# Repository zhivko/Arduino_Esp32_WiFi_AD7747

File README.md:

# D-duino-32(ESP32&0.96OLED display) & AD7747

This is simple Arduino 1.8 sketch that runs on https://www.tindie.com/products/lspoplove/d-duino-32esp32-and-096oled-display/
and uses:
graphic arduino lib for oled (https://github.com/squix78/esp8266-oled-ssd1306)
websockets library (https://github.com/bbx10/arduinoWebSockets)
hash library required by websockets (https://github.com/bbx10/Hash_tng.git)

Reads distance via capacity sensor AD7747:
(reference: http://opensourceecology.org/wiki/Paul_Log#Tue_Jul_30.2C_2013)
and streams data as standard websocket server that runs on esp32 on port 81.

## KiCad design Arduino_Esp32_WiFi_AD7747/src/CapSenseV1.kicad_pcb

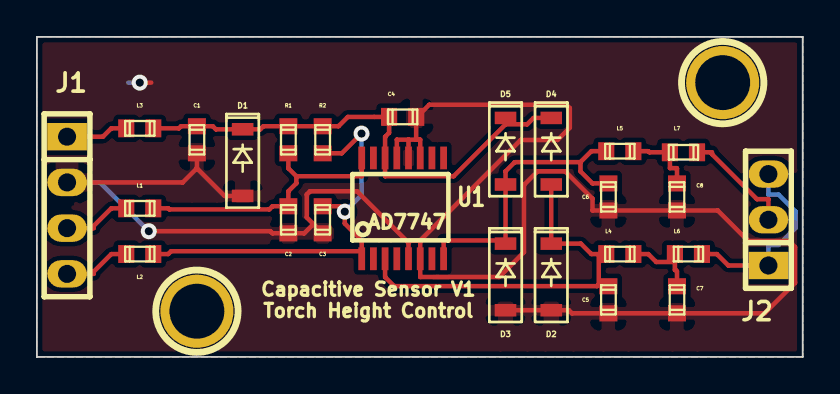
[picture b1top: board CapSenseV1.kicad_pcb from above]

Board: 2 copper layers, 42.5 x 17.8 mm, 25 parts (0 on the bottom side), 13 nets.

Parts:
C1: 2.2uF; c_0603
C2, C3: 10pf; c_0603
C4: 2.2uf; c_0603
C5, C6: 0.5pF; c_0603
C7, C8: 0.5pf; c_0603
D1: 6V; SOD123
D2, D3, D4, D5: 70V; SOD123
J1: HEADER_4; pin_strip_4
J2: HEADER_3; pin_strip_3
L1, L2, L3, L4, L5, L6, L7: 1k Z; r_0603
R1, R2: 4.7k; r_0603
U1: AD7747; TSSOP16

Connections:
/CapSense: J2.2, L7.2
/F_CapSense: C6.1, D3.2, D5.1, L5.1, U1.8
/F_SCL: C3.1, L2.2, R2.2, U1.1
/F_SDA: C2.1, L1.2, R1.2, U1.16
/F_Shield: C5.1, D2.2, D4.1, L4.1, U1.3
/F_VCC: C1.1, C4.1, D1.2, D4.2, D5.2, L3.2, R1.1, R2.1, U1.14
/GND: C1.2, C2.2, C3.2, C4.2, C5.2, C6.2, C7.2, C8.2, D1.1, D2.1, D3.1, J1.2, U1.5, U1.6, U1.11, U1.12, U1.13
/SCL: J1.4, L2.1
/SDA: J1.3, L1.1
/Shield: J2.1, J2.3, L6.2
/VCC: J1.1, L3.1
unnamed: C8.1, L5.2, L7.1
unnamed: C7.1, L4.2, L6.1

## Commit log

2017-08-20 new file: .gitignore new file: .travis.yml new file: Arduino_Esp32_WiFi_AD7747/.gitignore new file: Arduino_Esp32_WiFi_AD7747/.travis.yml new file: Arduino_Esp32_WiFi_AD7747/lib/esp8266-oled-ssd1306 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
2017-08-20 modified: Arduino_Esp32_WiFi_AD7747/src/Arduino_Esp32_WiFi_AD7747.ino
2017-08-20 modified: README.md
2017-08-27 modified: Arduino_Esp32_WiFi_AD7747/src/750px-CapSenseV1.png modified: Arduino_Esp32_WiFi_AD7747/src/Arduino_Esp32_WiFi_AD7747.ino new file: Arduino_Esp32_WiFi_AD7747/src/Arduino_Esp32_WiFi_AD7747.in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
2017-08-27 modified: Arduino_Esp32_WiFi_AD7747/src/Arduino_Esp32_WiFi_AD7747.ino modified: Arduino_Esp32_WiFi_AD7747/src/script.js
2017-08-30 modified: Arduino_Esp32_WiFi_AD7747/src/Arduino_Esp32_WiFi_AD7747.ino modified: README.md
